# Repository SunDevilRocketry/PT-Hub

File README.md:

<h1>PT Hub</h1>

<p>PCB Revision: 1.0</p>
<p>PCB Part No: L0006</p>

<p><b>Working Directory Structure:</b></p>

<p>
   doc: documentation
   
   src: source design files, e.g. schematic and PCB layout files

   lib: libraries for schematic symbols and footprints

   production: files needed for pcb fabrication, e.g. gerbers, profile, drill file

   sim: simulation models/files 

   cad: 3d models
  
   img: images of circuit/footprints for github display 
</p>

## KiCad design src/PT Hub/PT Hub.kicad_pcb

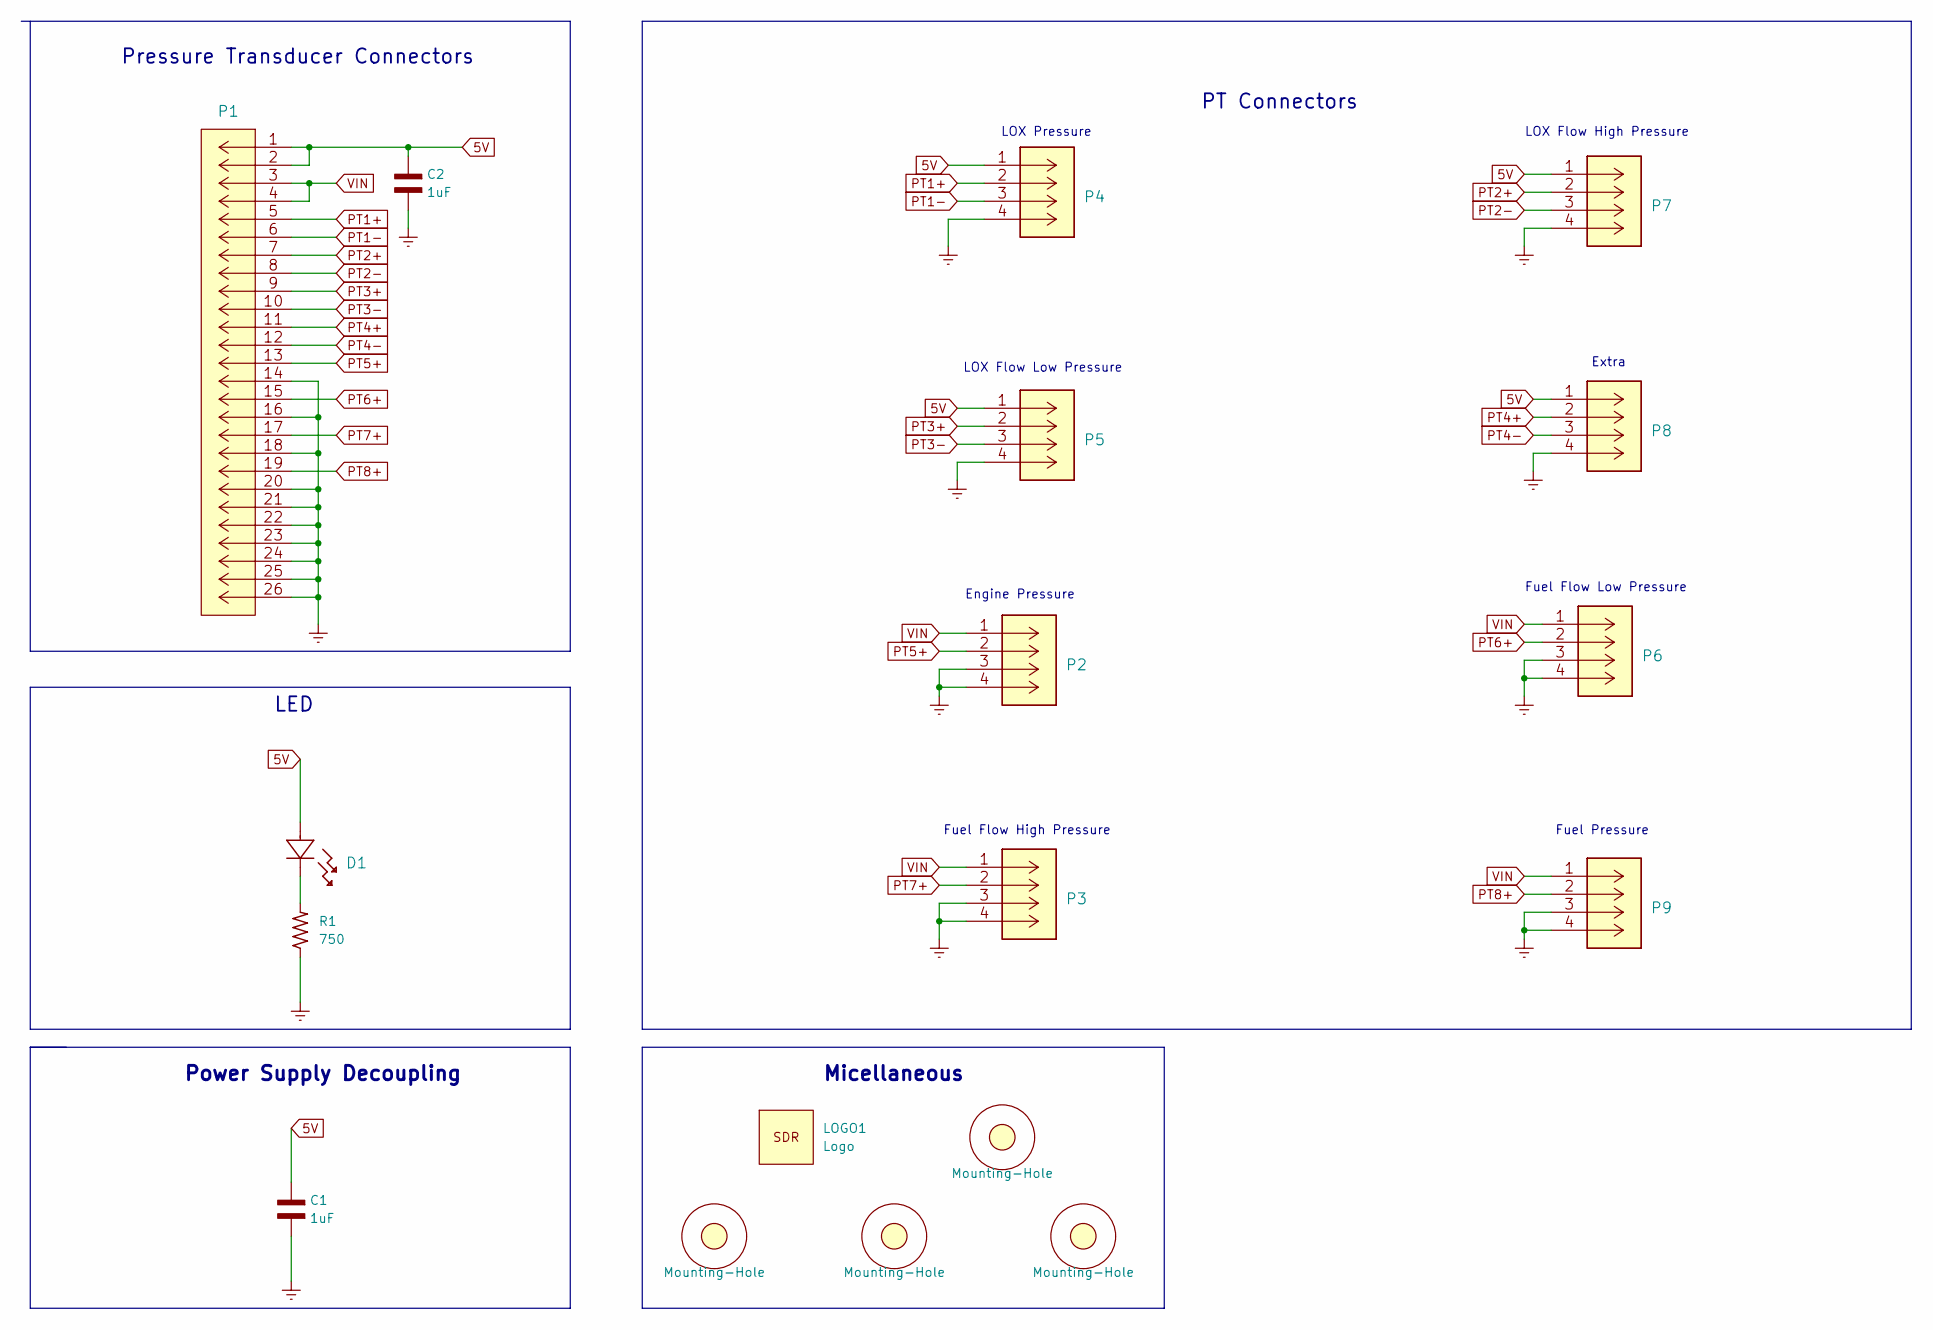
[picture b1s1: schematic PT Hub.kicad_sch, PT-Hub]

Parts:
C1, C2: 1uF; CAP_0603
D1: SML-LX1206GC-TR
H1, H2, H3, H4: Mounting-Hole; MountingHole_4.3mm_M4_DIN965
LOGO1: Logo
P1: 20021511-00026T4LF
P2, P3, P4, P5, P6, P7, P8, P9: 39299043
R1: 750; RES_0603

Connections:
5V: C1.1, C2.1, D1.2, P1.1, P1.2, P4.1 (+12V), P5.1 (+12V), P7.1 (+12V), P8.1 (+12V)
Earth: C1.2, C2.2, P1.14, P1.16, P1.18, P1.20, P1.21, P1.22, P1.23, P1.24, P1.25, P1.26, P2.3, P2.4, P3.3, P3.4, P4.4, P5.4, P6.3, P6.4, P7.4, P8.4, P9.3, P9.4, R1.1
unnamed: D1.1, R1.2
PT1+: P1.5, P4.2 (GND)
PT1-: P1.6, P4.3
PT2+: P1.7, P7.2 (GND)
PT2-: P1.8, P7.3
PT3+: P1.9, P5.2 (GND)
PT3-: P1.10, P5.3
PT4+: P1.11, P8.2 (GND)
PT4-: P1.12, P8.3
PT5+: P1.13, P2.2 (GND)
PT6+: P1.15, P6.2 (GND)
PT7+: P1.17, P3.2 (GND)
PT8+: P1.19, P9.2 (GND)
VIN: P1.3, P1.4, P2.1 (+12V), P3.1 (+12V), P6.1 (+12V), P9.1 (+12V)

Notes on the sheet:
Power Supply Decoupling
Fuel Flow Low Pressure
Engine Pressure
Pressure Transducer Connectors
PT Connectors
Fuel Flow High Pressure
LOX Pressure
Extra
Fuel Pressure
Micellaneous
LOX Flow High Pressure
LED
LOX Flow Low Pressure

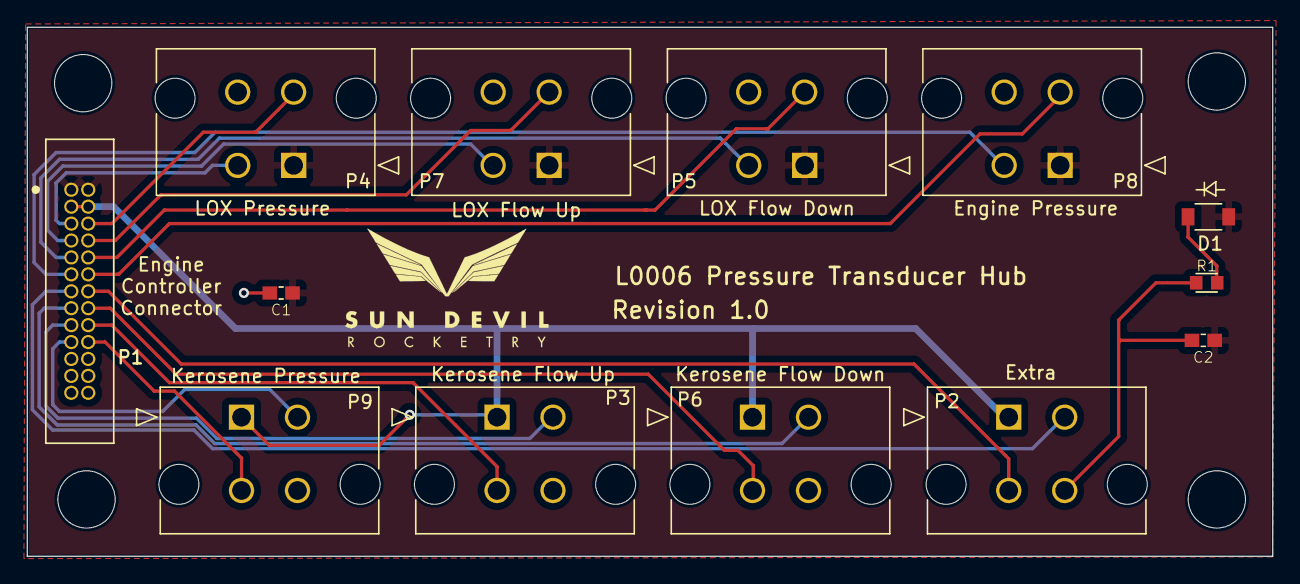
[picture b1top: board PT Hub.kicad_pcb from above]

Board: 2 copper layers, 93.5 x 39.7 mm, 18 parts (0 on the bottom side), 16 nets.

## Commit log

2022-05-09 created directory structure
2022-05-09 added basic info to readme
2022-05-29 New libraries for PT-Hub.
    New libraries for PT-Hub.
2022-05-29 added resistor to lib file
2022-06-05 CAD files added in
    added CAD files to PT Hub on KiCad
2022-06-12 schematic changes PT Hub
    schematic changes before switching to new git hub
2022-06-23 Test push
    test
2022-06-23 pls work
    pls
2022-06-23 sc
    shcematic
2022-06-23 1 symbol
2022-06-23 copy paste again
2022-06-26 footprints and PDB editor started
2022-07-01 most recent PCB changes as of 7/1
    PT Hub PCB changes
2022-07-01 PT Hub PCB changes
2022-07-02 rerouted PCB to handle ground plane discontinuities
2023-04-04 modified PT hub to be usable with hybrids PTs
2023-04-08 generated step file

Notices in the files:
parts and their libraries:
Copyright 2021 Accelerated Designs. All rights reserved.
